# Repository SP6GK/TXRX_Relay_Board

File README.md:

# TXRX_Relay_Board
A PCB for switching the signal path between RX and TX in a high-power HF amplifier, such as the Forte 600. It includes RX/TX relays, an input SWR bridge, and analog input over power protection.

For the theory of operation and functionality, please refer to section 2.2.1 of the Forte 600 documentation [link](https://github.com/SP6GK/Forte-600-HF-RF-Amplifier/blob/main/Optimization_HF_amplifier_TLT_Forte600Documentation.pdf).

## Change log:
### 05.09.2024 - rev 1.2:
- Removed unconnected tracks and fixed some footprint libraries, as well as the relative path to the custom schematic template (thanks to vk4kyt for pointing this out).
- Changed NPN and PNP transistors to more common types.
- Added coupler measurements and simulated the overpower protection circuit in Falstad.

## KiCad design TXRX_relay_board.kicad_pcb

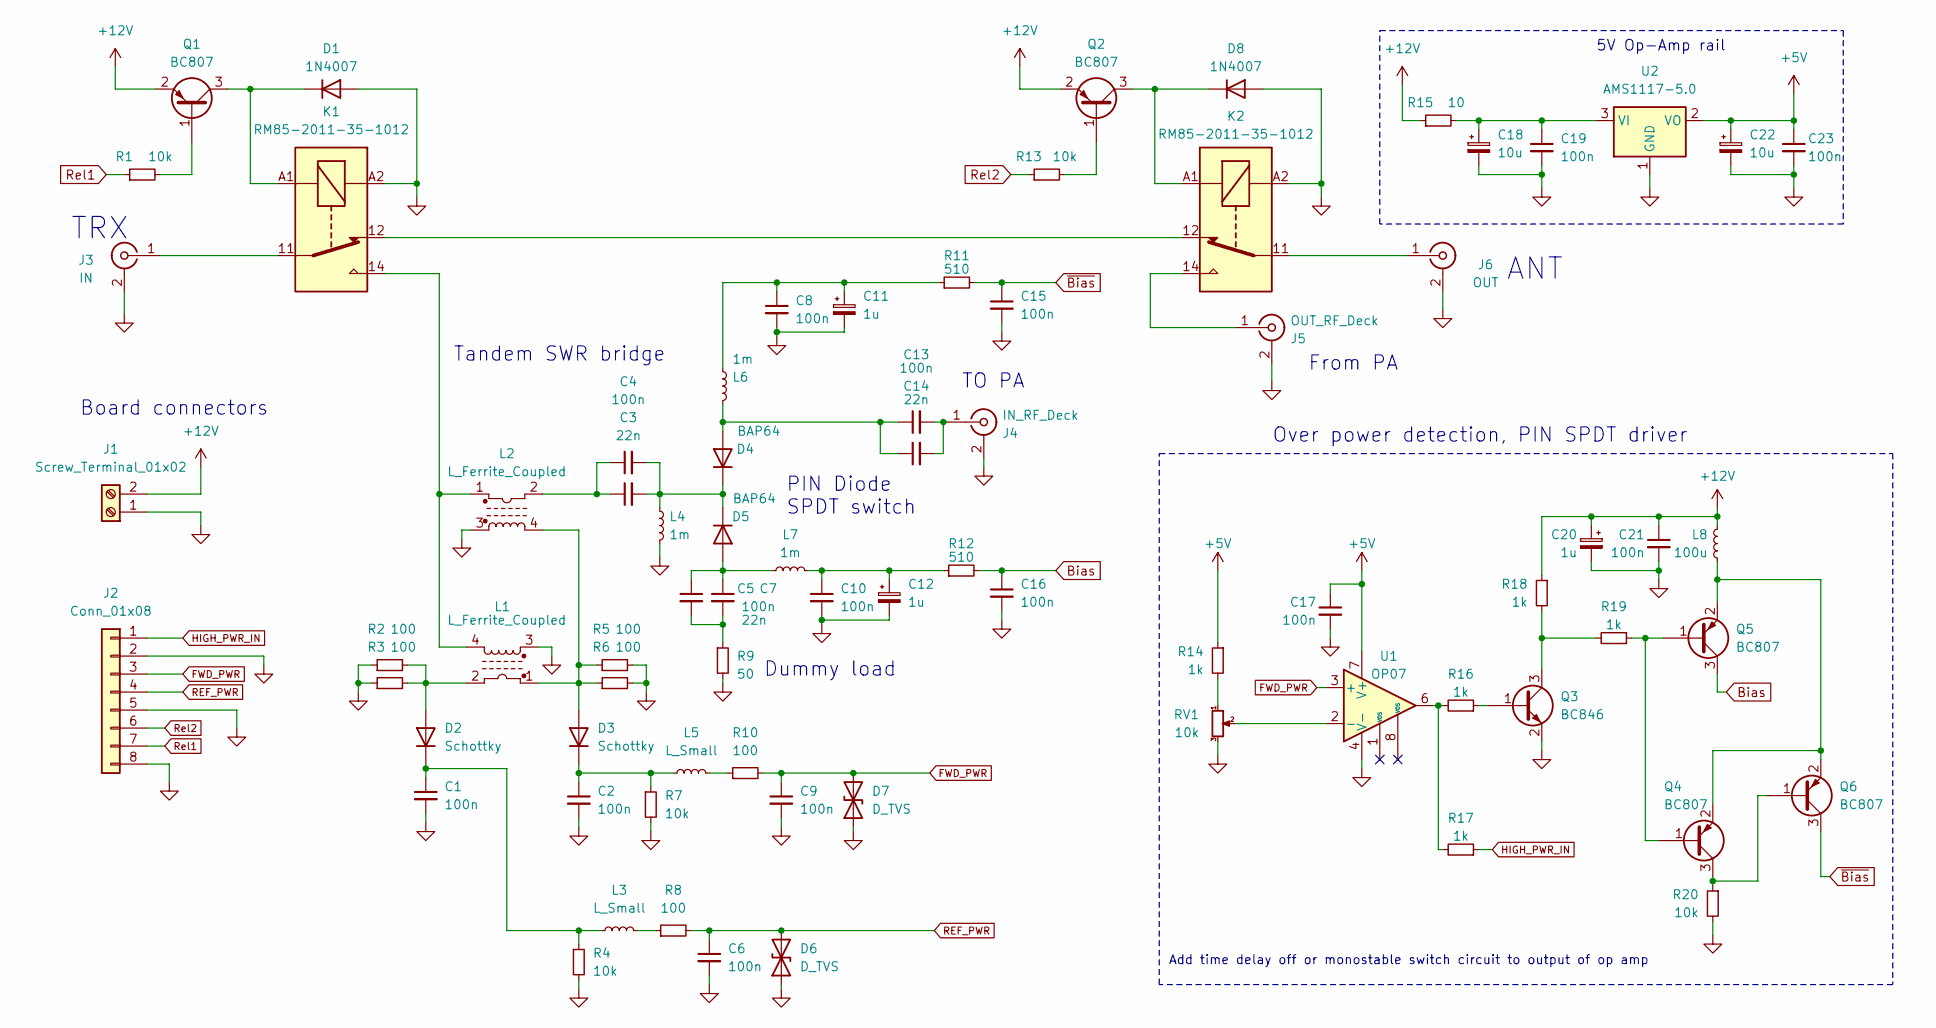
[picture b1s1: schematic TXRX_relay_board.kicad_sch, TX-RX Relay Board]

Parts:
C1, C2, C6, C8, C9, C10, C15, C16, C17, C19, C21, C23: 100n; C_0603_1608Metric_Pad1.08x0.95mm_HandSolder
C3, C5, C14: 22n; C_0805_2012Metric_Pad1.18x1.45mm_HandSolder
C4, C7, C13: 100n; C_0805_2012Metric_Pad1.18x1.45mm_HandSolder
C11, C12, C20: 1u; C_0805_2012Metric_Pad1.18x1.45mm_HandSolder
C18, C22: 10u; C_0805_2012Metric_Pad1.18x1.45mm_HandSolder
D1, D8: 1N4007; D_SMA
D2, D3: Schottky; D_SMA
D4, D5: BAP64; D_SOD-323_HandSoldering
D6, D7: D_TVS; D_SOD-323
J1: Screw_Terminal_01x02; TerminalBlock_bornier-2_P5.08mm
J2: Conn_01x08; JST_EH_B8B-EH-A_1x08_P2.50mm_Vertical
J3: IN; SMA_Amphenol_901-144_Vertical
J4: IN_RF_Deck; SMA_Amphenol_901-144_Vertical
J5: OUT_RF_Deck; Coax_solder
J6: OUT; Coax_solder
K1, K2: RM85-2011-35-1012; Relay_SPDT_Schrack-RT1-16A-FormC_RM5mm
L1, L2: L_Ferrite_Coupled; FT82_trafo
L3, L5: L_Small; L_0603_1608Metric_Pad1.05x0.95mm_HandSolder
L4, L6, L7: 1m; L_1812_4532Metric_Pad1.30x3.40mm_HandSolder
L8: 100u; C_1206_3216Metric_Pad1.33x1.80mm_HandSolder
Q1, Q2, Q4, Q5, Q6: BC807; SOT-23
Q3: BC846; SOT-23
R1, R4, R7, R13, R20: 10k; R_0603_1608Metric_Pad0.98x0.95mm_HandSolder
R2, R3, R5, R6: 100; R_2010_5025Metric_Pad1.40x2.65mm_HandSolder
R8, R10: 100; R_0603_1608Metric_Pad0.98x0.95mm_HandSolder
R9: 50; SMA_Amphenol_901-144_Vertical
R11, R12: 510; R_1206_3216Metric_Pad1.30x1.75mm_HandSolder
R14, R16, R17, R18, R19: 1k; R_0603_1608Metric_Pad0.98x0.95mm_HandSolder
R15: 10; R_2010_5025Metric_Pad1.40x2.65mm_HandSolder
RV1: 10k; Potentiometer_Bourns_3296W_Vertical
U1: OP07; SOIC-8_3.9x4.9mm_P1.27mm
U2: AMS1117-5.0; SOT-223-3_TabPin2

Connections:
+5V: C17.1, C22.1, C23.1, R14.1, U1.7 (V+), U2.2 (VO)
+12V: C20.1, C21.1, J1.2, L8.1, Q1.2 (E), Q2.2 (E), R15.1, R18.1
Bias: C16.1, Q5.3 (C), R12.2
FWD_PWR: C9.1, D7.2 (A2), J2.3, R10.2, U1.3 (+)
GND: C1.2, C2.2, C6.2, C8.2, C9.2, C10.2, C11.2, C12.2, C15.2, C16.2, C17.2, C18.2, C19.2, C20.2, C21.2, C22.2, C23.2, D1.2 (A), D6.1 (A1), D7.1 (A1), D8.2 (A), J1.1, J2.2, J2.5, J2.8, J3.2 (Ext), J4.2 (Ext), J5.2 (Ext), J6.2 (Ext), K1.A2, K2.A2, L1.3, L2.3, L4.2, Q3.2 (E), R2.1, R3.1, R4.2, R5.2, R6.2, R7.2, R9.2, R20.2, RV1.3, U1.4 (V-), U2.1 (GND)
HIGH_PWR_IN: J2.1, R17.1
unnamed: C3.1, C4.1, L2.2
unnamed: C5.2, C7.2, R9.1
unnamed: C10.1, C12.1, L7.2, R12.1
unnamed: C8.1, C11.1, L6.1, R11.1
unnamed: D1.1 (K), K1.A1, Q1.3 (C)
unnamed: D2.2 (A), L1.2, R2.2, R3.2
unnamed: C1.1, D2.1 (K), L3.1, R4.1
unnamed: D3.2 (A), L1.1, L2.4, R5.1, R6.1
unnamed: C2.1, D3.1 (K), L5.1, R7.1
unnamed: C13.1, C14.1, D4.2 (A), L6.2
unnamed: C3.2, C4.2, D4.1 (K), D5.1 (K), L4.1
unnamed: C5.1, C7.1, D5.2 (A), L7.1
unnamed: D8.1 (K), K2.A1, Q2.3 (C)
unnamed: J3.1 (In), K1.11
unnamed: C13.2, C14.2, J4.1 (In)
unnamed: J5.1 (In), K2.14
unnamed: J6.1 (In), K2.11
unnamed: K1.12, K2.12
unnamed: K1.14, L1.4, L2.1
unnamed: L3.2, R8.1
unnamed: L5.2, R10.1
unnamed: Q1.1 (B), R1.2
unnamed: Q2.1 (B), R13.2
unnamed: Q3.1 (B), R16.1
unnamed: Q3.3 (C), R18.2, R19.2
unnamed: Q4.1 (B), Q5.1 (B), R19.1
unnamed: Q4.3 (C), Q6.1 (B), R20.1
unnamed: L8.2, Q4.2 (E), Q5.2 (E), Q6.2 (E)
unnamed: R14.2, RV1.1
unnamed: R16.2, R17.2, U1.6
unnamed: RV1.2, U1.2 (-)
unnamed: C18.1, C19.1, R15.2, U2.3 (VI)
REF_PWR: C6.1, D6.2 (A2), J2.4, R8.2
Rel1: J2.7, R1.1
Rel2: J2.6, R13.1
~Bias: C15.1, Q6.3 (C), R11.2

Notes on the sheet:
Board connectors
5V Op-Amp rail
From PA
TRX
ANT
Dummy load
TO PA
PIN Diode SPDT switch
Tandem SWR bridge
Add time delay off or monostable switch circuit to output of op amp
Over power detection, PIN SPDT driver

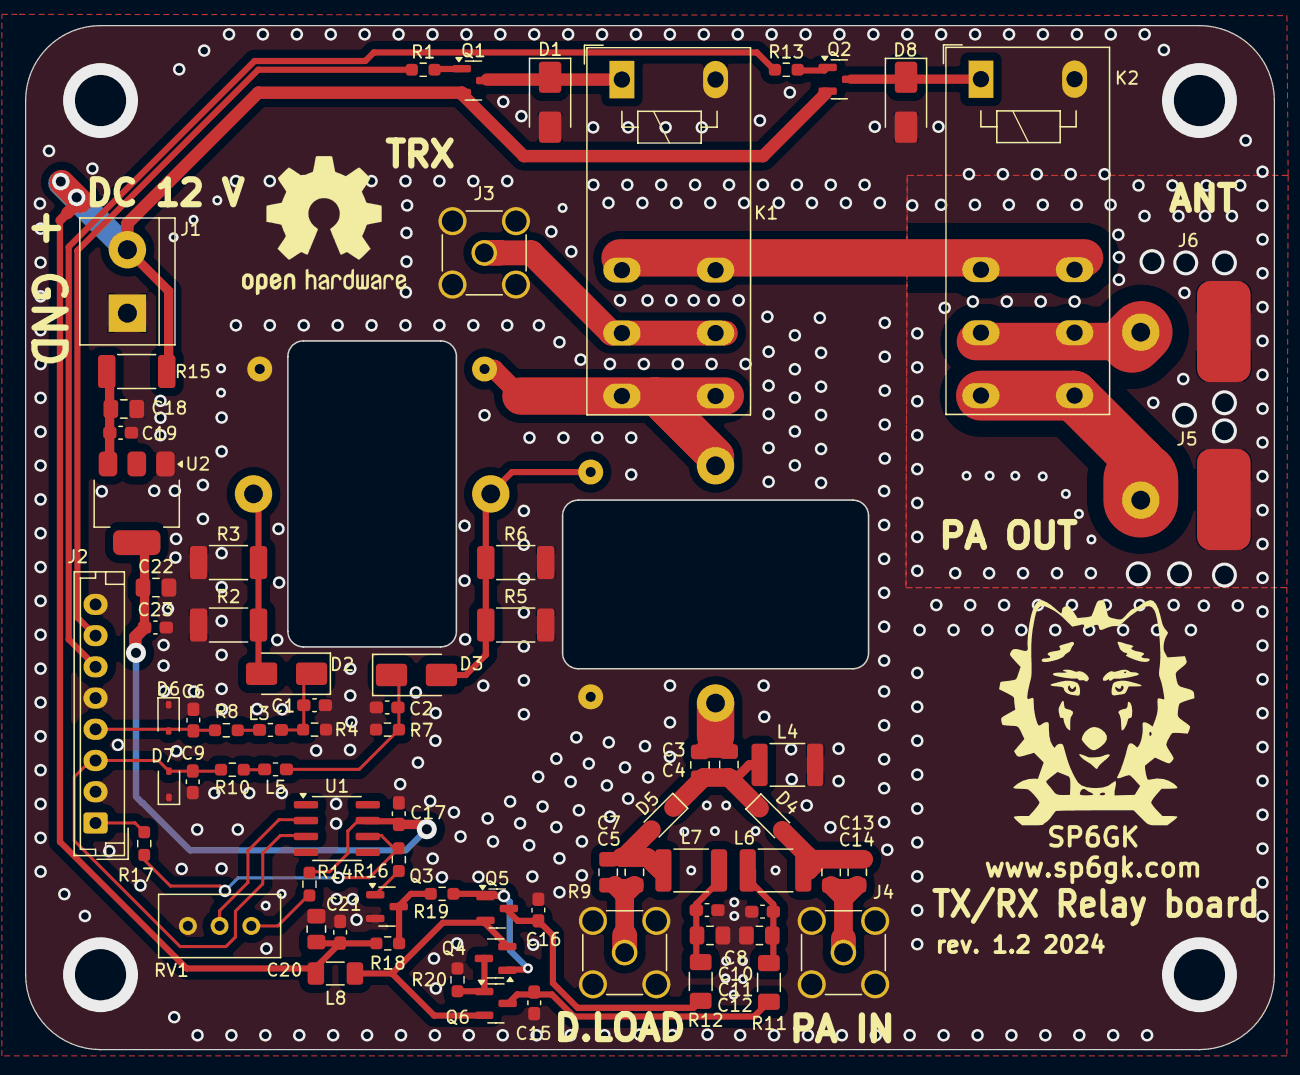
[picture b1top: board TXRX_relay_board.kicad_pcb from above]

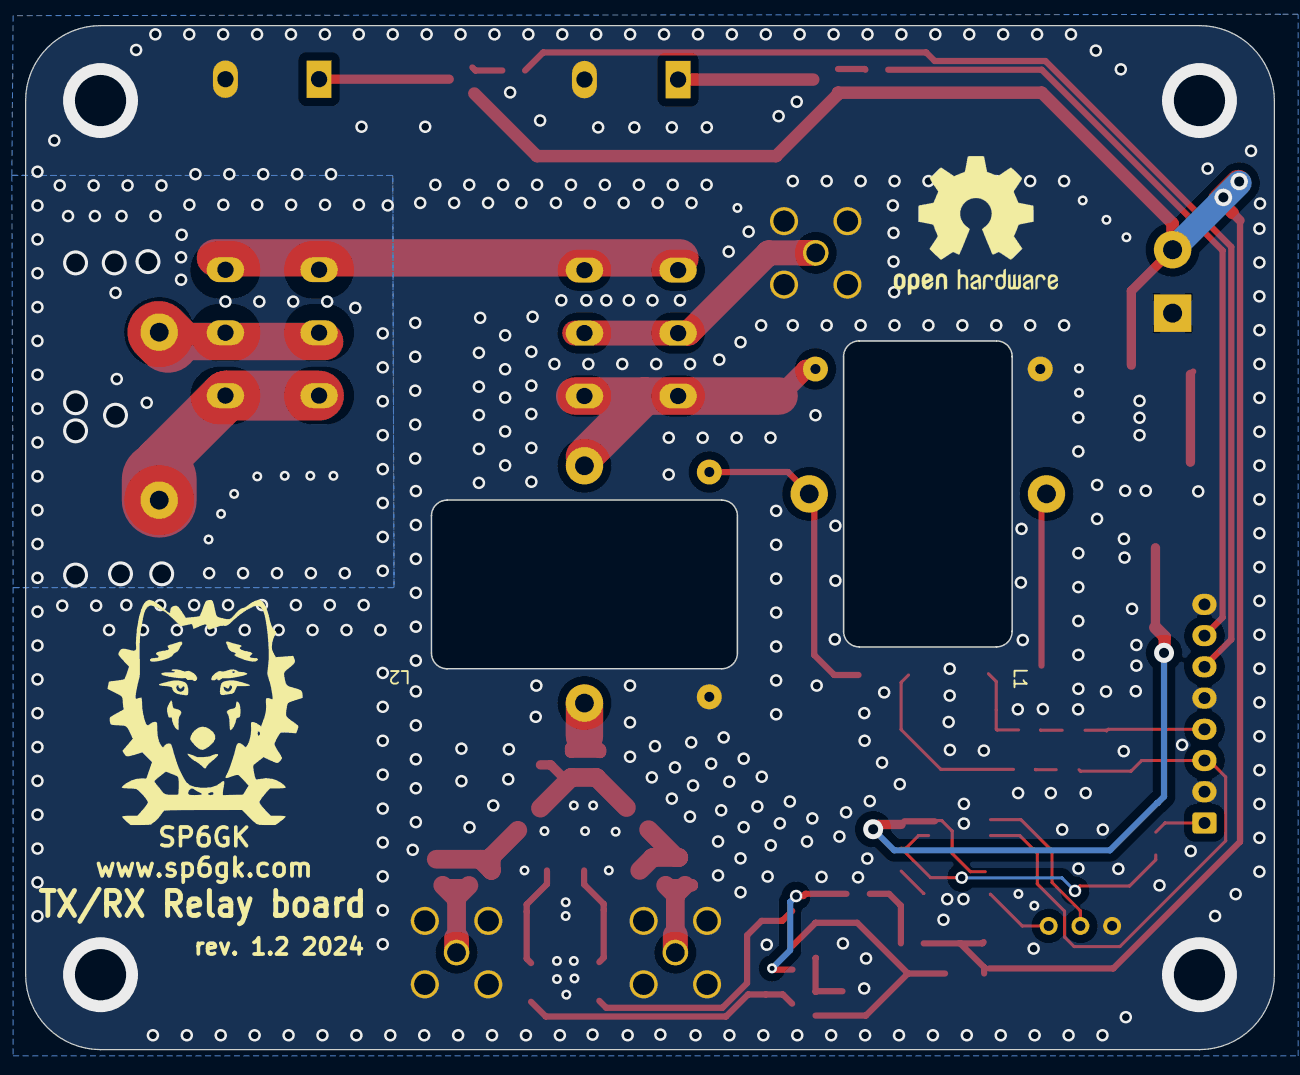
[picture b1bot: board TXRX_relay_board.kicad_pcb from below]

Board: 2 copper layers, 100.0 x 82.0 mm, 76 parts (2 on the bottom side), 42 nets.

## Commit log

2024-08-17 PCB photo
2024-09-05 rev 1.2
    Minor fixes, coupler measurements, falstad simulation of over power protection
2024-09-05 Update README.md
    change log rev 1.2
2026-02-01 Revision 1.2, fixed name of RLs, removed op amps in detector
